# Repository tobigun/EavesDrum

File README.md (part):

<p align="center">
  No matter if you are E(a)ve or Ste(a)ve - drumming for e(a)veryone
</p>

<p align="center">

</p>

<!-- vscode-markdown-toc -->
- [Welcome to EavesDrum!](#welcome-to-eavesdrum)
  - [Downloads](#downloads)
  - [EavesDrum Trigger Module](#eavesdrum-trigger-module)
- [Features](#features)
- [Before You Start: Is EavesDrum What You Need?](#before-you-start-is-eavesdrum-what-you-need)
- [Getting Started](#getting-started)
- [Build Your Own EavesDrum Trigger Module](#build-your-own-eavesdrum-trigger-module)
  - [Use the Reference Design](#use-the-reference-design)
    - [PCB Ordering and Assembly](#pcb-ordering-and-assembly)
    - [Connector Harness](#connector-harness)
      - [Connector Module](#connector-module)
      - [Build your own adapter](#build-your-own-adapter)
      - [Wiring the Single Pad Connectors](#wiring-the-single-pad-connectors)
  - [Make Your Own Design](#make-your-own-design)
    - [How the Circuit Works](#how-the-circuit-works)
      - [Over-Voltage Protection](#over-voltage-protection)
      - [Voltage Divider / DC Voltage Offset Generator](#voltage-divider--dc-voltage-offset-generator)
      - [Example](#example)
- [Configuration](#configuration)
  - [Calibration](#calibration)
  - [Settings](#settings)
    - [Generic Settings](#generic-settings)
    - [Pedal Settings](#pedal-settings)
    - [Apply Presets](#apply-presets)
  - [Mappings](#mappings)
  - [Apply a Whole Configuration](#apply-a-whole-configuration)
- [Understand and Reduce Latency](#understand-and-reduce-latency)
  - [Reduce Hit Detection Latency](#reduce-hit-detection-latency)
  - [Reduce Audio Interface Latency](#reduce-audio-interface-latency)
  - [TL;DR](#tldr)
- [Firmware Development](#firmware-development)
  - [How to Build the UI](#how-to-build-the-ui)
  - [How to Build the Backend and Firmware](#how-to-build-the-backend-and-firmware)
  - [How to Simulate a Drum-Kit on a PC](#how-to-simulate-a-drum-kit-on-a-pc)
- [FAQ](#faq)
    - [Windows 10 NCM device driver](#windows-10-ncm-device-driver)
- [About This Project](#about-this-project)
- [Other Related Projects](#other-related-projects)
- [Libraries](#libraries)
- [Author](#author)
- [License](#license)

<!-- vscode-markdown-toc-config
	numbering=false
	autoSave=true
	/vscode-markdown-toc-config -->
<!-- /vscode-markdown-toc -->

## Welcome to EavesDrum!

EavesDrum is an open-source e-drum trigger module project designed for drummers and makers.

It allows you to connect a multitude of drum pads or piezo triggers and convert their signals into MIDI events.

The configuration of the module is simple and user-friendly, thanks to a built-in WebUI. You can adjust sensitivity, threshold, and other parameters directly from your browser—no need for complicated software or direct hardware programming.

The trigger module acts as a USB MIDI device - simply connect it to your notebook and use drum software of your choice (EZdrummer, Addictive Drums, SSD5, ...) to convert your notebook into a complete drum module.

### Downloads
- Trigger Module:
  - [PCB files](https://github.com/tobigun/EavesDrum/releases/tag/PCB-module-v1.1.1)
  - [Firmware](https://github.com/tobigun/EavesDrum/releases/latest)
- [DIY Optical Hi-Hat Sensor](doc/hihat.md)

### EavesDrum Trigger Module

DIY ultra-low-volume metal mesh cymbal setup:

Conventional rubber cymbal setup:

Low-volume cymbal setup:

System overview:

## Features

- **Drum Trigger Inputs:**
  - With the EavesDrum PCB, you can connect your drum pads or piezo sensors to 32 analog inputs.
  - Each input can be mapped individually, for example to 16 TRS (3-pin Tip-Ring-Sleeve) connectors or 32 TS (2-pin Tip-Sleeve) connectors.
  - The [default configuration](#connector-harness) uses the following drum setup:
    - Snare (1x TRS for head/rim + 1x TS for side-rim)
    - 5x Toms (each with 1 TRS for head/rim)
    - Kick drum (1x TS)
    - Ride (1x TRS for bow/edge + 1x TS for cup)
    - 4x Cymbals (each with 1x TRS for bow/edge + 1x TS for cup)
    - Hi-Hat (1x TRS for bow/edge + 1x TS for cup)
    - Hi-Hat Pedal resistive or optical (connected to a dedicated connector with 3.3V or 5V supply voltage)
- **Compatibility:**
  -  EavesDrum is compatible with a wide range of [Roland (only non-USB), Yamaha, ATV and EFNOTE pads](#pad-connectors).
  -  The following pads were tested:
     - ATV XD-P10M/P13M 2-zone Drums
     - ATV aD-C14/C16/C18 3-zone Cymbals
     - EFNOTE EFD-S12P 3-zone Snare (head, rim, side-rim)
     - Roland PDX-8 2-zone Drum
     - Roland KD-10 Kick Pad
     - Zeitgeist ZG ECP 13" 3-zone Cymbal
     - Zeitgeist ZG CAD Cymbals (although the edge triggers unreliably due to the switch design)
     - Zeitgeist ZG ZKD7 Kick Pad
     - Drum-tec Hi-Hat controller (resistive)
     - DIY optical sensor (TCRT5000 based)
       - See sections below for schematics and Gerber files.
     - DIY drums and cymbals
       - See sections below for schematics and Gerber files.
- **MIDI Output:**
  - USB Device (Default)
    - Connect EavesDrum to a PC and use a Drum Software like EZdrummer or Superior Drummer to convert the trigger signals to high quality drum sounds. 
  - USB Host
    - Connect a USB device to EavesDrum, e.g. a Drum Module and trigger sounds on that device
      - Tested with a Yamaha EAD-10
      - Device must be compatible with USB Full-Speed device. This does not apply to EFNOTE's 3/5/7 devices as they require a USB High-Speed device.
  - DIN 5-Pin
    - Connect legacy drum modules or devices that still have a DIN 5-pin connector and trigger sounds on them.
  - Bluetooth LE Client (Pico2W only)
    - This can be used to connect to a device that can act as a Bluetooth LE MIDI Server, e.g. EFNOTE's 3/5/7 drum modules.
  - Bluetooth LE Server (Pico2W only)
    - Activate the BLE Server mode and connect a smartphone or tablet to EavesDrum and trigger sounds in an app. This can also be used to connect a computer wireless.
      - Android (smartphone): works, but most MIDI apps will require the "MIDI+BTLE" app to use BLE as they do not support it directly.
      - Windows (PC): does not support BLE MIDI out-of-the-box. You will need a BLE connector app like [BLE-MIDI Bridge](https://github.com/Maxime-J/BLE-MIDI-Bridge) or [MIDIberry](https://apps.microsoft.com/detail/9n39720h2m05) together with a virtual loopback MIDI cable software like [loopMIDI](https://www.tobias-erichsen.de/software/loopmidi.html).
      - iOS (iPad): works with Garage Band out of the box
  - Guitar Hero Drum-Kit (SPI)
    - If you have an old Guitar Hero Drum-Kit (e.g. for the Wii), attach EavesDrum to the controllers internal SPI connector and play Guitar Hero on your retro console with your modern drum kit.
- **MIDI Mappings:** 
  - Mappings are freely customizable via the UI.
  - It already contains Midi-Mappings for:
    - Addictive Drums 2
    - BFD Player 1.2
    - EZdrummer 3 (which can probably also be used as a base for your own Superior Drummer 3 mapping)
    - Superior Drummer 3
    - MT Power 2
    - Steven Slate Drums 5 (SSD5)
- **Low Latency:**
  - Latency is mainly determined by your audio interface and the selected scan time. With a decent audio interface, you can [reach a total latency of about 8ms](#latency).
  - You can measure the latency of your setup with the latency measurement feature built into the UI.
- **Affordable:** you might be able to make an assembled trigger module for approx. 20€.
  - See the section [Build your own EavesDrum trigger module](#use-the-reference-design).
- **Supported Microcontrollers:**
  - Raspberry Pi Pico2
  - Raspberry Pi Pico2W (comes with a WIFI and Bluetooth module)
    - Required for MIDI over Bluetooth LE.
    - Also provides a WIFI Access Point to reach the EavesDrum WebUI wirelessly. 

- **Open Source:** Source code and PCB Gerber files are available for customization and extension.
- **WebUI Configuration:** Browser-based interface for setting up and tweaking trigger parameters such as sensitivity, threshold, retrigger prevention, and more. No app required as the UI runs directly on the trigger module.
  - Monitor the signal of your drum pads in real time so that you can see the effect of your settings.

  - Provides extensive settings options within a (hopefully) user-friendly layout.

  - Mappings can be adjusted individually or for the whole kit.

## Before You Start: Is EavesDrum What You Need?
**EavesDrum is for you if you:**
  - need more / additional trigger inputs to those that standard drum kits support.
  - want to mix drums from different vendors as most drum kits only work well with their own pads.
  - want to start drumming and do not want to pay a fortune for a drum kit.
  - want to diagnose or improve the trigger behavior of your drum pad.
  - have fun making stuff and just want to build your own drum kit or implement your own drum module features.

**EavesDrum might not be for you if you:**
  - want to use the module for live performances as it does not give any guarantee error-free operation at all times or conditions.
  - want a drum module that works standalone without a Notebook.
  - want a drum module that works out-of-the-box, as you will have to tweak the settings according to your pads via the UI.
  - need cross-talk cancelation, positional sensing or decay curves, as these features are not implemented (yet).

> [!IMPORTANT]
> **Disclaimer:** Although EavesDrum has been tested with various drum pads and setups, it remains a DIY hardware project and may behave differently depending on your specific configuration. Connecting this module to your equipment is done at your own risk. I cannot be held liable for any damage, malfunction, or injury resulting from its use. Please ensure compatibility and take appropriate precautions before integrating it into your setup.

## Getting Started

0. **Prerequisites:**
All you need is:
    - A computer with a drum software (see [MIDI Mappings](#midi-mappings) to give you a short overview).
      - A PC or Mac is recommended.
        - Although there is no minimum requirement, a slow CPU might increase the [Latency](#latency).
        - USB and Bluetooth LE is supported
      - An Apple iPad with Garage Band also works - either with USB-C (or an Apple Camera Connection Kit for Lightning connectors) or with Bluetooth LE.
      -  Android smartphones / tablets also work (via USB or Bluetooth LE) but lack good drumming apps.
    - A decent audio interface with low latency, preferably one with dedicated ASIO drivers. See [the section about latency](#latency) for more information.
    - Something to drum on, i.e. drum pads, cymbals and a Hi-Hat pedal. Or just a cheap piezo if you want to DIY your own drum.

1. **Build the EavesDrum trigger module:**<br/>
   - Either built it yourself or order it via a PCB manufacturer of your choice.
   - See section [Build your own EavesDrum trigger module](#use-the-reference-design) for schematics and Gerber files.

2. **Download & Flash the firmware:**<br/>
   - [Download the firmware for your Pico board from the Release download section](https://github.com/tobigun/EavesDrum/releases/latest).
   - Press the BOOTSEL while connecting your Pico Board via USB to enter the bootloader mode.
   - The board will now be detected as an USB flash drive.
   - Drag & Drop the firmware .uf2 file onto the drive.
3. **Start the WebUI:**<br/>
   - Connect EavesDrum to a computer, tablet or smartphone
     - via USB: EavesDrum will be detected as a network device
     - via WIFI AccessPoint (only with Pico2W)
       - The AccessPoint (AP) can be activated by pressing and holding the WIFI button at power-up until the network LED lights up. For security and performance reasons, the AP is only active for one session until the module is powered down.
       - Connect to the AP named "EavesDrum". No credentials are required.
   - Open your browser and navigate to the WebUI by entering either
     - the static IP: http://192.168.7.1 (USB) or http://192.168.4.1 (WIFI AP)
     - the DNS name http://eaves.drum</a>.
     - **IMPORTANT**: if you are using Windows 10 you have to install the USB network drivers manually to reach the WebUI. See the [FAQ](#faq) section below for more info. 
4. **Calibrate:**<br/>
   - [Calibrate the voltage offset with the UI Wizard](#calibration)
5. **Connect Drums:**<br/>
   - Connect your drum pads or triggers to the EavesDrum hardware.
6. **Configuration:**<br/>
   - Adjust [settings](#settings) and [MIDI mappings](#mappings).
7. **Play:**<br/>
   - Once configured, start playing and enjoy!

## Build Your Own EavesDrum Trigger Module
### Use the Reference Design
**Schematics of the trigger module with 32 inputs:**

You can find the schematics and pcb files in the `schematics/module` directory. They can be viewed and edited with [KiCad](https://www.kicad.org/).

**Bill of material (BOM):**

| Component | Designator | Quantity | Price / Unit | Price Total | Comment |
| --------- | ---------- | -------- | ------------ | ----------- | ------- | 
| Raspberry Pi Pico 2(W)(H) | A1 | 1 | 5€ / W: 7.50€ | 5€ / W: 7.50€ | Use a Pico2W if you want WiFi and Bluetooth LE, otherwise a Pico2 is enough.<br>- There is also a "H" variant for ~1€ more with an already soldered header<br>- Pico1 is not recommended due its outdated performance. |
| 20-pin Header (male)<br>20-pin Header (female) | J4, J5 | 2 | 0.20€<br>0.30€ | 1.00€ | Optional but recommended. <br>- Socket your Pico so that it can be replaced if it is damaged or if you want to exchange it by another variant.<br>- The male header is not needed if one of the Pico "H" variants is used. |
| HC4067 | U1, U2 | 2 | 1.00€ | 2.00€ | Multiplexer. Each provides 16 inputs.<br>Available from many vendors with HC4067 in the name (e.g. CD74HC4067M). Make sure it is the SO-24 package. |
| BAT54S | D1.0 - D1.15<br>D2.0 - D2.15 | 32 | 0.05€ | 1.60€ |Prefer the ones with a forward voltage (VF) of 800mV@100mA over those with 1V@100mA but probably any vendor and type will work.|
| LED (red) | D3 | 1 | 0.08€ | 0.08€ | Use any color of your choice. THT or SMD 0805 / 0603 packages are supported. |
| LED (white/blue) | D4 | 1 | 0.10€ | 0.10€ | Use any color of your choice. THT or SMD 0805 / 0603 packages are supported. |
| LED (yellow) | D5 | 1 | 0.10€ | 0.10€ | Use any color of your choice. THT or SMD 0805 / 0603 packages are supported. |
| Push Switch | SW1, SW2, SW3 | 3 | 0.15€ | 0.45€ |6x6mm. Only the `RESET` button is used at the moment. |
| Potentiometer 5k | R3, R6 | 2 | 0.35€ | 0.70€ | Supports Piher PT10 (10mm) / PT6 (6mm) or Bourns TC33 (SMD) |
| Potentiometer 100k | R11 | 1 | 0.35€ | 0.35€ | Supports **only** Piher PT6 (6mm) or Bourns TC33 (SMD) |
| Resistor 10 Ohms | R17 | 1 | 0.03€ | 0.03€ | SMD 0805 package, 125mW, 1%.<br>For MIDI 5-pin DIN connector |
| Resistor 33 Ohms | R18 | 1 | 0.03€ | 0.03€ | SMD 0805 package, 125mW, 1%.<br>For MIDI 5-pin DIN connector |
| Resistor 330 Ohms | R5, R8, R13 | 3 | 0.03€ | 0.09€ | SMD 0805 package, 125mW, 1% |
| Resistor 1 kOhms | R1.0 - R1.15<br>R2.0 - R2.15 | 32 | 0.015€ | 0.48€ | SMD 0805 package, 125mW, 1% |
| Resistor 2.7 kOhms | R4 | 1 | 0.03€ | 0.03€ | SMD 0805 package, 125mW, 1% |
| Resistor 4.7 kOhms | R9, R14 | 2 | 0.03€ | 0.06€ | SMD 0805 package, 125mW, 1%.<br>Use different values to adjust brightness of LEDs D3 (R9) and D5 (R14) to your liking. |
| Resistor 10 kOhms | R10 | 1 | 0.03€ | 0.03€ | SMD 0805 package, 125mW, 1%<br>Use different value to adjust brightness of LED D4 to your liking. |
| Resistor 15 kOhms | R15, R16 | 1 | 0.03€ | 0.06€ | SMD 0805 package, 125mW, 1%.<br>For USB-Host connector |
| Capacitor 10 µF | C1, C2 | 2 | 0.04€ | 0.08€ | SMD 0805 package, >=25V, X5R (or X7R)
| D-Sub HD 44-pin Connector, right-angled, female | J0 | 1 | 2.50€ | 2.50€ | Alternatively, you can use any connector of your choice via the 2x25 pin IDC header (J2). |
| USB-A socket, right-angled | J1 | 1 | 0.15€ | 0.15€ | Socket for USB-Host. |
| Header 2x25 pins (male) | J2 | 1 | 0.33€ | 0.33€ | Expansion port (Optional).
| 3-Pin Header (female) | J3 | 1 | 0.15€ | 0.15€ | UART serial debug output.
| DIN 5-pin female 180° | J7 | 1 | 0.85€ | 0.85€ | Connector for MIDI Serial DIN Output. |
| PCB | - | 1 | ~5€ (Germany) | ~5€ | See the section [PCB Ordering and Assembly](#pcb-ordering-and-assembly) for more info|
| **Total** |||| ~22€ || 

If you are located in Germany, check prices at Reichelt (that's where the prices from above are from), Pollin, Conrad. Globally Mouser and Farnell might be your friend.

#### PCB Ordering and Assembly
All you need to order your Trigger Module PCB for assembly are the following files:
- GERBER File
- BOM File (Bill of Material)
- CPL File (Component Placement List)

These files are available on the [PCB Module 1.2 Release Page](https://github.com/tobigun/EavesDrum/releases/tag/PCB-module-v1.2).

**To order the PCB:**
- Open the website of a PCB manufacturer.
  - The most famous ones are probably JLCPCB and PCBWay from China.
  - There is also Aisler (Germany), EuroCircuits (Europe) and probably more if you want to produce your PCB in Europe instead of China.
  - Choose whatever suits you best.
- Upload the GERBER zip-file. The site should show you a preview of the PCB now.
- You can leave the default settings.
  - (Recommended) Change `Surface Finish` from `HASL (with lead)` to `LeadFree HASL` to protect our environment from toxic lead
- For delivery "EuroPacket" or "Global (Standard) Direct" might be your choice.
  - Both variants will ship your PCBs together with other PCBs in a big package to an importer in your home country (or a neighbored country). The package will then be split into smaller packages and sent to you. This is cheaper and will probably also save you the hassle of customs as this will be done by the importer.
  - The shipment time is a bit longer than with other more expensive delivery options. But with all options the parcel will probably spent several days in the customs office, so time savings is not that much noticable.

*Examples:*
- JLCPCB: 4€ - Coupons + Shipping/Taxes
  - Shipping to Germany: Global Standard Direct: 1.50€ / EuroPacket: 5.50€ + Tax: ~1€
- PCBWay: 5€ - Coupons + Shipping/Taxes
  - Shipping to Germany: ~5€ with Global Direct + Tax: ?

Due to the varying discount by coupons, prices of JLCPCB and PCBWay my vary. So check both.

**Assembly**
It is possible to assemble the PCB on your own by hand-soldering without special equipment. The only tricky part is the HC4067 SMD packages and the SMD resistors and capacitors. While the latter is quite easy, the HC4067 requires some experience.

You can also let JLCPCB or PCBWay assemble the PCB as you already order the PCB there.

*Example:*
- JLCPCB: 5 assembled PCBs including parts cost about 106€ (excl. shipping/tax), so approx. 21€ per PCB.
  - Note that the minimum amount of assembled PCBs per order is 2

If you want an assembled board it is best to organize a collective purchase order to split the cost. I created a [forum discussion where you can organize an order](https://github.com/tobigun/EavesDrum/discussions/1).

**To order an assembled PCB:**
- Perform the same steps as for the normal PCB but select "PCB Assembly".
- If you use JLCPCB in the next step you are asked for the BOM and CPL files that you have to upload.
- Some parts might currently not be available. There is most likely an identical component / chip from a different vendor that you can select in this case.
- In the next step check the component placements and submit your order.
- After a review an engineer might contact you if there are questions about the design (that was the case in my order).

> [!NOTE]
> Also take a look at the [DIY Optical Hi-Hat Sensor PCB](doc/hihat.md). You might want to get both PCBs with one order.

#### Connector Harness

In addition to the trigger module you will have to build an adapter to connect the drum pads.

##### Connector Module

The easiest way to achieve this is to build the connector module:

You can find more information about the connector and the files to order the (assembled) PCB on the  
[connector release page](https://github.com/tobigun/EavesDrum/releases/tag/PCB-connector-v1.0).

##### Build your own adapter

But you can also build your own adapter. Here is the pin out of the D-Sub HD 44 pin connector:

The pin names consist of the multiplexer input IDs (in1_x: input x of Multiplexer MP1, in2_x: input x of Multiplexer MP2).

You can either solder jacks directly to a D-Sub connector or you can build an adapter to one of the cable harnesses that come with drum modules.

This is the default configuration for the outputs:

| Jack | Pins | Assignment |
|-----------|------|------------|
|1| in1_0, in1_1, in1_2 | Snare (Main, Rim, Side-Rim) |
|2| in1_3, in1_4 | Tom 1 (Main, Rim) |
|3| in1_5, in1_6 | Tom 2 (Main, Rim) |
|4| in1_7, in1_8 | Tom 3 (Main, Rim) |
|5| in1_9 | Kick Drum |
|6| in1_10, in1_11, in1_12 | Ride (Bow, Edge, Cup) |
|7| in1_13, in1_14, in1_15 | Cymbal 1 (Bow, Edge, Cup) |
|8| in2_0, in2_1, in2_2 | Cymbal 2 (Bow, Edge, Cup) |
|9| in2_3, in2_4, in2_5 | Cymbal 3 (Bow, Edge, Cup) |
|10| in2_6, in2_7, in2_8 | Hi-Hat (Bow, Edge, Cup) |
|11| in2_9, in2_10 | Tom 4 (Main, Rim) |
|12| in2_11, in2_12 | Tom 5 (Main, Rim) |
|13| in2_13, in2_14, in2_15 | Cymbal 4 (Bow, Edge, Cup) |
|Pedal| adc2, +3.3V/5V (optical only) | Hi-Hat Pedal (resistive or optical)<br>- For resistive controllers: adjust the `ADC2 DC offset` potentiometer to the (+) direction (~4kOhm)<br>- For optical (TCRT5000) controllers: adjust the `ADC2 DC offset` potentiometer to the middle (~69kOhm)<br>This will adjust the sensitivity of the ADC2 channel. You can fine-tune this setting in the UI later. |

> [!INFO]
> The layout for the older D-Sub 37 pin connector of board revisions v1.1.x can be found [here](https://github.com/tobigun/EavesDrum/tree/PCB-module-v1.1.1#connector-harness)

##### Wiring the Single Pad Connectors

The wiring of **Snares and Toms** is straightforward in most cases
- Almost all companies use the Roland style 2-Piezo 1xTRS layout
- Yamaha uses switches for Edge and Side Rim
- EFNote adds a dedicated Side-Rim zone with another Piezo

<table>
<thead>
  <tr>
    <th>Tom/Snare</th>
    <th>Main/Head (Piezo)</th>
    <th>Edge</th>
    <th>Side-Rim</th>
    <th>EavesDrum Setting</th>
  </tr>
</thead>
<tbody>
  <tr><td>Generic 1-Zone</td><td>Tip</td><td>-</td><td>-</td><td>Drum / 1-Zone / Piezo</td></tr>
  <tr><td>Roland 2-Zone</td><td>Tip</td><td>Ring</td><td>- (Cross-Stick sound is generated by module)</td><td>Drum / 2-Zones / 2 Piezos</td></tr>
  <tr><td>Yamaha 3-Zone</td><td>Tip</td><td colspan='2'>Ring (Switches for zones are multiplexed by a 10k resistor)</td><td>Drum / 3-Zones / Piezo + 2 Switches (1x TRS)</td></tr>
  <tr><td>EFNOTE 3-Zone</td><td>Tip (Main Jack)</td><td>Ring (Main Jack)</td><td>Tip (Side-Rim Jack)</td><td>Drum / 3-Zones / 3 Piezos</td></tr>
</tbody>
</table>

**Cymbals** (with 3-Zones) follow two main connection styles:
- Roland style with 2x TRS Jacks (labeled "Bow/Edge" and "Bow/Bell")
- Yamaha style with 1x TRS Jack. Bell and Cup switch connected to the "Ring" pin (multiplexed by a 10k resistor)

If you have only a one or two zone cymbal the pin layout is the same for both vendors.

<table>
<thead>
  <tr>
    <th>Cymbal</th>
    <th>Bow (Piezo)</th>
    <th>Edge Switch</th>
    <th>Bell/Cup Switch</th>
    <th>EavesDrum Setting</th>
  </tr>
</thead>
<tbody>
  <tr><td>Generic 1-Zone</td><td>Tip</td><td>-</td><td>-</td><td>Cymbal / 1-Zone / Piezo / No Choke</td></tr>
  <tr><td>Generic 2-Zone</td><td>Tip</td><td>Ring</td><td>-</td><td>Cymbal / 2-Zones / Piezo + Switch / Choke: Edge</td></tr>
  <tr><td>Roland 3-Zone</td><td>Tip (Jack "Bow/Edge")</td><td>Ring (Jack "Bow/Edge")</td><td>Ring (Jack "Bow/Bell")</td><td>Cymbal / 3-Zones / Piezo + 2 Switches (<b>2x</b> TRS) / Choke: Edge</td></tr>
  <tr><td>Yamaha 3-Zone</td><td>Tip</td><td colspan='2'>Ring (multiplexed by a 10k resistor)</td><td>Cymbal / 3-Zones / Piezo + 2 Switches (<b>1x</b> TRS) / Choke: Edge</td></tr>
</tbody>
</table>

See also:
- [Cymbal wiring diagram at edrums.github.io](https://edrums.github.io/en/diy/cymbal_switch/) for the wiring difference between Roland and Yamaha cymbals.
- [Yamaha compatibility matrix](https://de.yamaha.com/de/download/files/2094396/) for an overview of the Tom and Cymbal models

### Make Your Own Design

In case you do not want to use the reference design or you just need a few inputs, you can also design your own trigger module and just use the firmware.
The base circuit for each input consists of the following parts:

Please note that "~2,7k" for R1 in the schematics means that the variable resistor should be adjusted to this value. The nominal value of the resistor should be about 5k to have some range for the adjustment.

You might also be able to build this on a breadboard for first experimentation.

#### How the Circuit Works
Skip this section if you are not interested in the electronic background of the circuit.

##### Over-Voltage Protection
- Two clamping diodes restrict the signal to the range between 0V - 3.3V
  - Protects the ADC input pins of the microcontroller
  - Prevents cross-talk between inputs if a Multiplexer (e.g. 74HC4067) is used
- Note that Schottky diodes with a low forward voltage have to be used here
  - They react faster than a conventional (Silicon P-N-junction) diode to over voltage spikes
  - The BAT85, BAS85 (SMD variant of the BAT85) and BAT54S (two diodes in one SMD package) diodes work fine

##### Voltage Divider / DC Voltage Offset Generator
- The resistors R1 and R2 form a voltage divider that halfs the operation voltage (Vcc=3.3V) to generate a ~1.65V DC offset voltage
  - This is necessary to sample the full signal with its positive and negative half-wave
  - Note that R1 is a variable resistor (potentiometer) as the circuit is usually not that perfect that R1=R2 gives you half the operation voltage as it should in theory
- Together with R3, R1 and R2 scale the voltage of the piezo to the range of 0V - 3.3V that can be sampled by the ADC
  - This is necessary as the voltages of a piezo can be rather high.
  - If you want to play with the values there is an [LTSpice simulation here](doc/simulation/drum-trigger.asc) but keep in mind that the piezo model does not act like a real one.
- Simpler approaches without an offset voltage are also possible, e.g. by just clamping the signal with a zener diode to just keep the positive half-wave of the signal
    - Although this works, you will have to pay attention to the polarity of the piezos
    - If the piezo starts with a negative half-wave, you will miss it and thus will add latency of approx. 1ms
    - This is even worse, if you use two piezos for head and rim, as the wrong zone might be triggered if the first half-wave of one piezo is missing but missing for the other.

##### Example
Here is a simple example with a high intensity hit on a snare drum: The left shows the input signal that is offset by 1.65V and it fits nicely into the 0V - 3.3V range. On the right you see the display in the UI. All the details of the signal are maintained. Note that the firmware maps the negative part of the signal to the positive y-axis so that the thresholds can be edited more easily.

## Configuration

### Calibration
Before you can start you have to first adjust the DC voltage offset so that the signal level is at 0% when no pad is hit. But no panic - the process is easy and only has to be done once.

For this open the WebUI, open the settings page (should be open by default) and click on `Calibrate` in the `Monitor` panel and follow the instructions.

At the beginning the signal graph will probably look like this, with a signal level above 0% (here 10%):

Now turn the potentiometer labeled `ADC0 DC offset` (R3) with a screwdriver. Only if turned in the correct direction, the signal level will decrease, otherwise it will increase. So turn the potentiometer until the signal level reaches 0%. If you turned too much, the signal level will increase again - in this case turn in the opposite direction.

The signal graph should now look like this - with a signal level of 0%:

Now the calibration is completed.

> [!NOTE]
> Do not worry if the signal is not totally clean and has a bit of a ripple in the 1% or 2% range. This can be compensated with the thresholds later.
> If you do not reach the 0% level at all, your trigger module might be faulty.

### Settings

To optimize the trigger behavior for your pad, go to the settings page and open the panel of the pad you want to adjust.

First assure that the Drum type (here: Drum / 3-Zones / 3 Piezos) is correct. If you are not sure, check [the section about the different pad connectors](#pad-connectors) to see what the type should be.

Mark the pad as monitored (the record button on the right top of the pad's panel). This way you can see the signal graph (left) and hit graph (right) in the `Monitor` panel whenever you hit the monitored pad. Right next to the hit graph is the hit history which shows you the last hits. You can also click on one of the last hits to see the graphs again.

If you click on `Show All Pads` on the top, you can see hits on every pad, no matter if it is monitored or not.

#### Generic Settings

- **Main/Head/Rim/Edge/Cup/... Range**: trigger range for each zone
  - The **min. value of the range** specifies the sensitivity.
    - You should set it as low as possible without having the pad trigger when you do not hit it.
  - The **max. value of the range** specifies the signal level that marks 100%.
    - Set it in a way that you can reach a signal level of 100% when you hit the pad the hardest way you would in your playing style.
    - If you set the max. too low, the detected signal level will be 100% even if you did not hit the pad with the highest intensity.
  - If you enable monitoring for the pad it should be easy to find the correct values.
  - For cymbals with switches for edge and cup you will only have a **minimum threshold** for each switch instead of a range.
    - This determines at which level the switch is considered to be closed or opened.

- **Scan Time**: Determines the time to search for a peak (Scan phase).
- **Mask Time**: Blocks hit detection for the given time (Mask phase).
  - Can be used to reduce false retriggers.
  - The Mask phase starts after the Scan phase.
  - The Mask is applied to all zones of the pad.
- **Decay Time**: Blocks hits with a hit velocity below the given decay curve (Decay phase).
  - In contrast to the Mask phase that blocks all hits, this only blocks hits selectively.
  - It can be used to define a longer decay phase where reverberations of the last hit can be blocked but new hits are still possible if they are strong enough.
  - The Decay phase starts after the Mask phase.
  - The Decay curve is applied to all zones of the pad.
- **Decay Curve**: The curve that defines how the detection threshold decreases during the decay phase.
  - **Linear**: The further the decay phase progresses, the lower the required hit strength becomes for a hit to be detected. 
    - The phase begins with a detection threshold equal to the highest signal value detected during the scan phase (the peak).
    - It ends with a detection threshold equal to the minimum detection threshold.
    - Throughout the decay phase, the threshold is linearly reduced from the peak value down to the minimum threshold.
- **Curve Type**: Lets you change the trigger behavior for low or high intensity hits, i.e. you can shift the sensitivity more to the lower or higher intensities.
- **Head/Rim Bias**: Sets whether to prefer head or rim sound when the signals of both to not indicate a clear winner.
  - This is useful to assure that rimshots trigger the rim sound.
  - Move the bias more to the rim (i.e. to the right), the rim zone will more likely be triggered if both zones were hit at once.
  - Only available for drums (i.e. snares and toms) with at least two zones.

> [!IMPORTANT]
> When you change settings they will be applied immediately but they will be reset to the old values when EavesDrum reboots or loses power. To keep the settings you have to save them with the "Save" Button (SD-Card icon) in the top Icon Bar.

#### Pedal Settings
The settings for the Hi-Hat pedal are different from the settings of the pads.

- **Pedal Range**: determines the offset and threshold for the lowest and highest signal level
  - Do not touch the Hi-Hat pedal for the open position.
  - Adjust the **min value** of the `Pedal Range` so that the corresponding marker in the monitor's signal graph is slightly above the current pedal signal and the Pedal value in the hit graph is at 0%.
  - Next, close the Hi-Hat pedal.
  - Now adjust the **max value** of the `Pedal Range` so that the corresponding marker in the monitor's signal graph is slightly below the current signal and the hit graph shows 100%.
  - When you move the pedal now, you should get the full range between 0% and 100% in the hit graph, and it should stay at 0% when open and at 100% when closed.
- **Move Detection Tolerance** this determines how much the pedal has to be moved to change its value. A smaller tolerance gives you a higher resolution but is more prone to noise in the signal.
  - Press the Hi-Hat pedal to a position between open and closed. Try to keep this position - the value in the hit graph should not change. If it does, you might decrease the tolerance until the hit graph value is stable.
- **Pedal State Thresholds** and **Chick Detect Timeout**:
  - When the pedal travels from the `Almost Closed` position to the `Closed Position` a "Chick" sound detection takes place.
  - The faster the pedal moves from `Almost Closed` to `Closed` the higher the intensity of the "Chick" sound will be.
  - If the time between both states is higher than **Chick Detect Timeout**, then no sound will be played.
  - If you do not want a "Chick" sound, you can disable it on the Mappings Page by setting the sound for the "Chick" to `None`.

To see the effect of the settings, monitor the pedal with the record button:

#### Apply Presets
In the folder `config/presets` you can find some presets for some pads. You can apply them by dragging them from Windows Explorer to the settings panel of a pad.

### Mappings

With the Mappings page you can change the MIDI mappings of each pad.

Select the MIDI note of the zone to the desired value. You can trigger the note via the UI by pressing the "Play" button to preview the sound.

> [!IMPORTANT]
> When you change mappings they will be applied immediately but they will be reset to the old values when EavesDrum reboots or loses power. To keep the settings you have to save them with the "Save" Button (SD-Card icon) in the top Icon Bar.

**Apply Drum-Kit Mappings**
You can change the mappings of all pads in the drum-kit at ones if you drag & drop a mapping file (see folder `/config/mappings`) to top border (aka the Icon Bar) of the UI. This way you can switch between the mappings of the drum softwares easily.

Alternatively you can also click on the "Apply Config File" button in the top Icon Bar to open the same file drop area that appears if you drag & drop a file.

If you drag & drop the mappings file onto a pad instead of the top bar, only this pad's mappings will be changed:

**Roles**
Note that the mappings are assigned to a `role` (e.g. Snare, Tom1, ...) and not to a pad directly. As the drum kits differ in number and type of pads it would be rather difficult to have generic mapping files if there is no common denominator for every drum. This is what the role is for: it specifies the role of the drum in the drum kit, so that you have the correct mappings assigned to the drum when you switch from one mapping file to another.

### Apply a Whole Configuration
If you want to have more control over a configuration you can download the active configuration with the "Download" icon in the top Icon Bar. Then do you modifications on the downloaded YAML file and upload it again by either clicking on the "Apply Config File" button in the Icon Bar or by Drag & Drop of the config to the Icon Bar.

This way you can Backup & Restore your config whenever you do a firmware update.

## Understand and Reduce Latency
At a speed of sound of about 343 m/s, the sound travels 34 cm in 1 ms, so a little less then the length of a drum stick. It seems that everything up to [5 ms is not noticeable and most drummers still have no problem with 10 ms](https://forums.steinberg.net/t/ab-welcher-latenz-bemerkt-ihr-eine-verzogerung-und-ab-wann-stort-die-euch/105517/45). So you want the latency to be as low as possible or at least below 10 ms.

If you look at the signal path there a quite some components involved from the hit to the drum until you hear the sound from the speaker. This is round trip time (RTT) of your system which defines the latency of your signal.

1. The **hit detection** by the trigger module will take a fixed time - the scan time that you selected in the pad's settings and that is by default 3 ms.
1. The time it takes the trigger module to **generate and transfer a MIDI message to the computer via USB** is negligible as it is only a small fraction of a ms.
2. Although the **sound processing** might also take some time I did not notice a vast differences between the drum softwares.
3. The audio latency from your drum software to the **audio interface** is the biggest contributor to latency.

### Reduce Hit Detection Latency
The time the trigger module waits for a peak to detect a hit can be configured for each pad. The default of 3 ms was chosen so that it works with most drum pads.

If you take a look at the screenshot of the Monitor below you might notice that the piezo signal for some pads reaches its peaks only after 1, 2 or even 3 ms. 

So if you set the scan time too low, you might get wrong results. Decrease the scan time in small amounts and check if the hit strength are still detected correctly.

### Reduce Audio Interface Latency
The Audio Interface latency depends on the **number of buffers** the software, drivers and audio interface uses and the **buffer size**.
  - Dedicated audio interfaces for musicians are optimized for low latency and offer better (ASIO) drivers.
  - The bigger the buffer the less error-prone is the playback, even if the CPU is currently doing some other stuff. But every buffer and every byte in the buffer will increase the latency.

The best way to reduce latency is to **reduce the buffer sizes**. The goal is a **latency of 5-6 ms** for this part of the signal chain.
  - On **Windows** this is **only possible** without crackling and dropouts **with ASIO drivers**. So make sure your audio device has dedicated ASIO drivers.
  - Do not waste your time with **WASAPI** or **DirectSound** drivers. WASAPI (Low-Latency) resulted in 69ms, WASAPI (Exclusive Mode) in 34.9ms. DirectSound was even worse. Same device with ASIO was about 6ms.
  - You can try **[ASIO4All](https://asio4all.org/)** if you want to start with an existing interface that does not come with ASIO drivers - but keep your expectations low. With the Realtek soundcard built into one of my notebooks I could not get the latency below 35 ms with ASIO4All which is unusable.

**Select ASIO as the output type** in your drum software and start with the lowest audio buffer size.
  - Trigger the pads really quick and try every pads if you hear some crackling or dropouts on any of them.
  - Also check if the audio quality is still ok or if it sounds muffled, ...
  - If you notice audio problems (**crackling, muffling, popping, dropouts**)
    - Make sure that no other CPU-intensive software is currently in use.
    - Also make sure that your CPU is suited for the task (i.e. you CPU load is not too high)
    - Although my old Intel Core i7-7500U (2.7 GHz) Ultrabook CPU from 2016 works fine as drum computer most of the time, it seems to stutter sometimes if I select the lowest buffer size. Something I have not noticed with my newer Intel Core i7-1260P (2.1 GHz, 12 Cores) from 2022.
    - If you have a modern i7 (and probably i5) CPU you should be fine. Same with an Apple M1 CPU.
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
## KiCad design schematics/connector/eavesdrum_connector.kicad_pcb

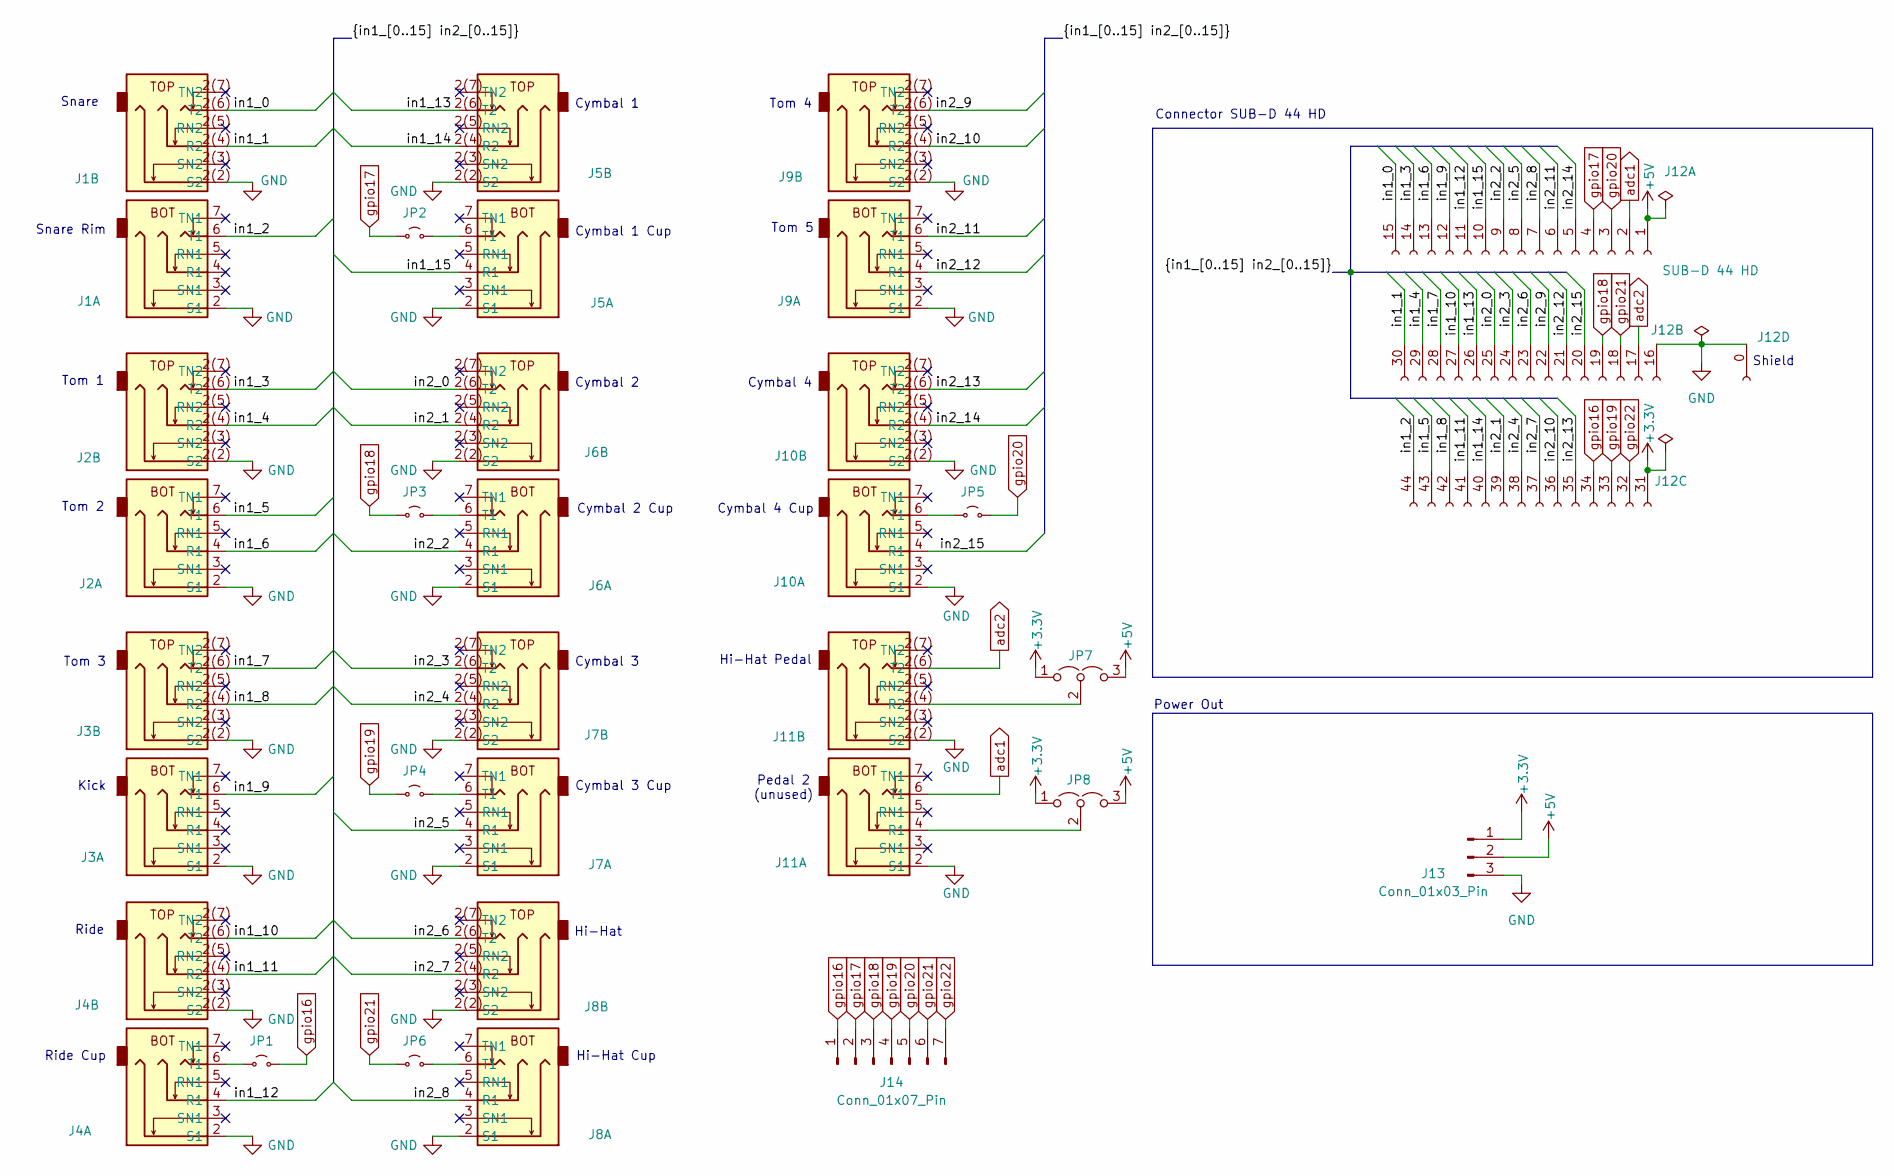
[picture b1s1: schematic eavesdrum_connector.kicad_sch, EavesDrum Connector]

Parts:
J1, J2, J3, J4, J5, J6, J7, J8, J9, J10, J11: AudioJack3_Dual_Ground_Switch; PJ-625K
J12: SUB-D 44 HD; DSUB-44-HD_Pins_Horizontal_P2.29x2.54mm_EdgePinOffset8.35mm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
J13: Conn_01x03_Pin; TerminalBlock_WAGO_233-503_2x03_P2.54mm
J14: Conn_01x07_Pin; TerminalBlock_WAGO_233-507_2x07_P2.54mm
JP1, JP2, JP3, JP4, JP5, JP6: Jumper_2_Small_Open; PinHeader_1x02_P2.54mm_Vertical
JP7, JP8: Jumper_3_Open; PinHeader_1x03_P2.54mm_Vertical

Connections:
+3.3V: J12.31, J13.1, JP7.1 (A), JP8.1 (A)
+5V: J12.1, J13.2, JP7.3 (B), JP8.3 (B)
/in1_0: J1.2(6) (T2), J12.15
/in1_1: J1.2(4) (R2), J12.30
/in1_2: J1.6 (T1), J12.44
/in1_3: J2.2(6) (T2), J12.14
/in1_4: J2.2(4) (R2), J12.29
/in1_5: J2.6 (T1), J12.43
/in1_6: J2.4 (R1), J12.13
/in1_7: J3.2(6) (T2), J12.28
/in1_8: J3.2(4) (R2), J12.42
/in1_9: J3.6 (T1), J12.12
/in1_10: J4.2(6) (T2), J12.27
/in1_11: J4.2(4) (R2), J12.41
/in1_12: J4.4 (R1), J12.11
/in1_13: J5.2(6) (T2), J12.26
/in1_14: J5.2(4) (R2), J12.40
/in1_15: J5.4 (R1), J12.10
/in2_0: J6.2(6) (T2), J12.25
/in2_1: J6.2(4) (R2), J12.39
/in2_2: J6.4 (R1), J12.9
/in2_3: J7.2(6) (T2), J12.24
/in2_4: J7.2(4) (R2), J12.38
/in2_5: J7.4 (R1), J12.8
/in2_6: J8.2(6) (T2), J12.23
/in2_7: J8.2(4) (R2), J12.37
/in2_8: J8.4 (R1), J12.7
/in2_9: J9.2(6) (T2), J12.22
/in2_10: J9.2(4) (R2), J12.36
/in2_11: J9.6 (T1), J12.6
/in2_12: J9.4 (R1), J12.21
/in2_13: J10.2(6) (T2), J12.35
/in2_14: J10.2(4) (R2), J12.5
/in2_15: J10.4 (R1), J12.20
GND: J1.2 (S1), J1.2(2) (S2), J2.2 (S1), J2.2(2) (S2), J3.2 (S1), J3.2(2) (S2), J4.2 (S1), J4.2(2) (S2), J5.2 (S1), J5.2(2) (S2), J6.2 (S1), J6.2(2) (S2), J7.2 (S1), J7.2(2) (S2), J8.2 (S1), J8.2(2) (S2), J9.2 (S1), J9.2(2) (S2), J10.2 (S1), J10.2(2) (S2), J11.2 (S1), J11.2(2) (S2), J12.0 (Pin_44), J12.16, J13.3
unnamed: J4.6 (T1), JP1.1 (A)
unnamed: J5.6 (T1), JP2.1 (A)
unnamed: J6.6 (T1), JP3.1 (A)
unnamed: J7.6 (T1), JP4.1 (A)
unnamed: J8.6 (T1), JP6.1 (A)
unnamed: J10.6 (T1), JP5.1 (A)
unnamed: J11.4 (R1), JP8.2 (C)
unnamed: J11.2(4) (R2), JP7.2 (C)
adc1: J11.6 (T1), J12.2
adc2: J11.2(6) (T2), J12.17
gpio16: J12.34, J14.1, JP1.2 (B)
gpio17: J12.4, J14.2, JP2.2 (B)
gpio18: J12.19, J14.3, JP3.2 (B)
gpio19: J12.33, J14.4, JP4.2 (B)
gpio20: J12.3, J14.5, JP5.2 (B)
gpio21: J12.18, J14.6, JP6.2 (B)
gpio22: J12.32, J14.7

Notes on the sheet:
Hi-Hat Cup
Connector SUB-D 44 HD
Snare
Shield
Ride Cup
Cymbal 2
Hi-Hat
Kick
Pedal 2 (unused)
Cymbal 4
Ride
Tom 3
Cymbal 1
Cymbal 2 Cup
Snare Rim
Tom 5
Power Out
Cymbal 4 Cup
Cymbal 1 Cup
Cymbal 3 Cup
Tom 1
Tom 4
Hi-Hat Pedal
Tom 2
Cymbal 3

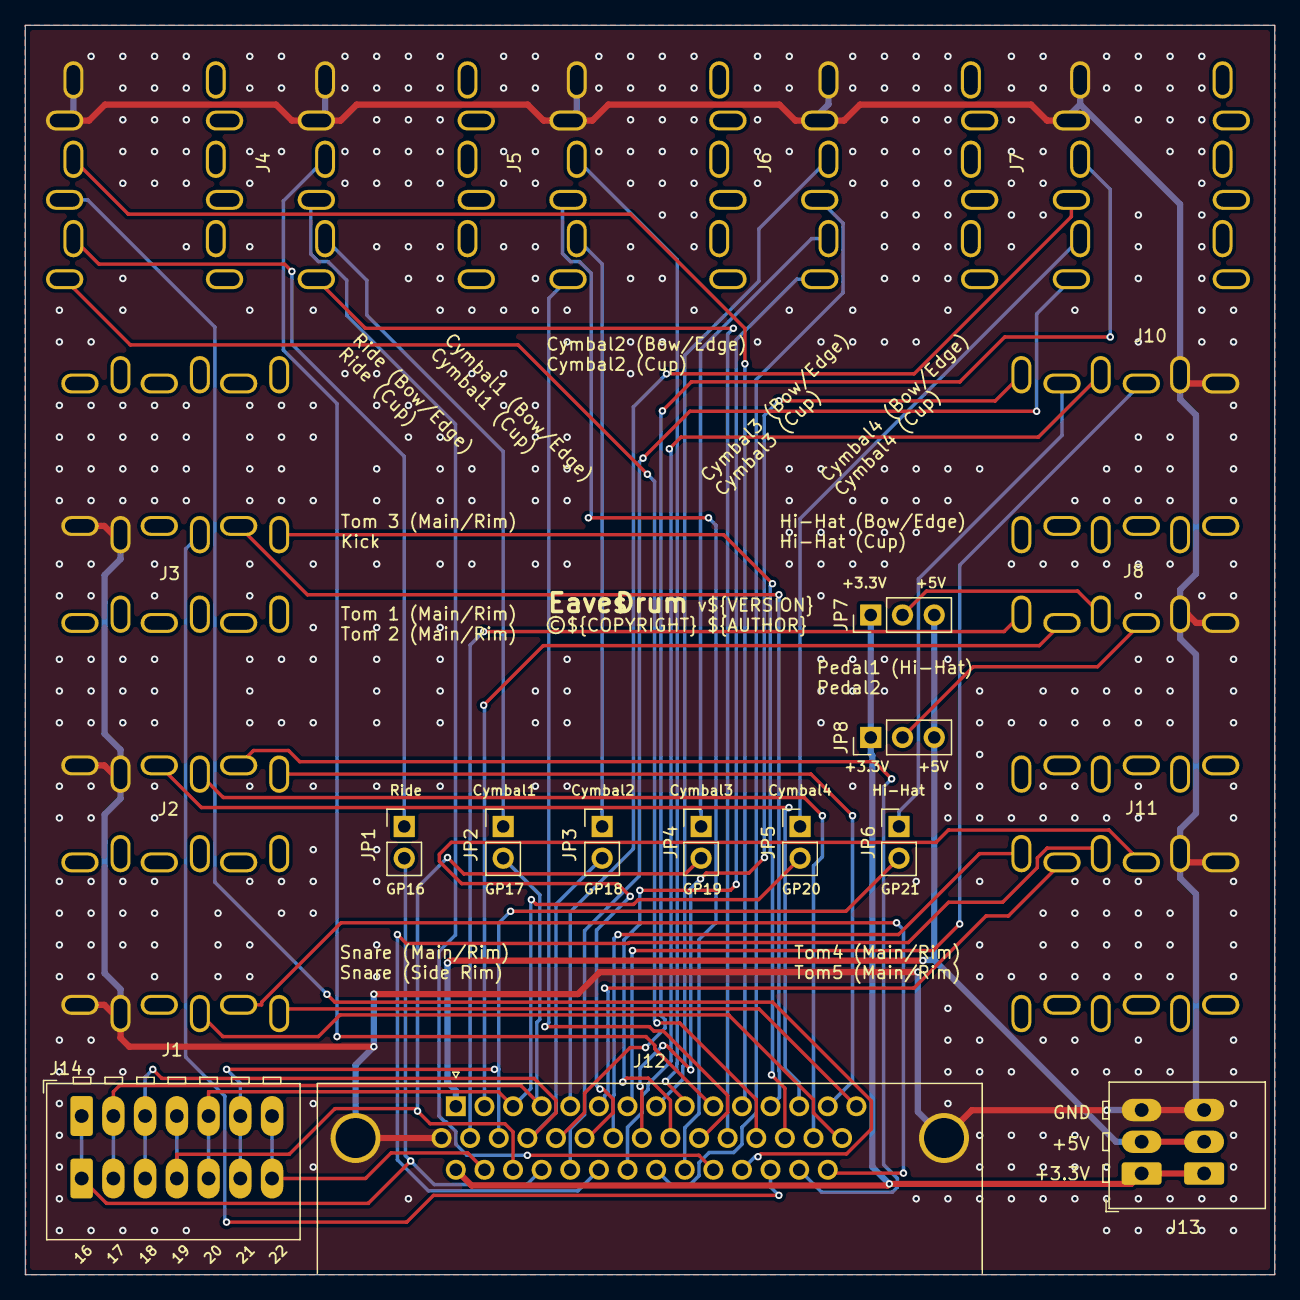
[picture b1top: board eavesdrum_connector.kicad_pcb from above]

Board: 2 copper layers, 100.0 x 100.0 mm, 22 parts (0 on the bottom side), 52 nets.

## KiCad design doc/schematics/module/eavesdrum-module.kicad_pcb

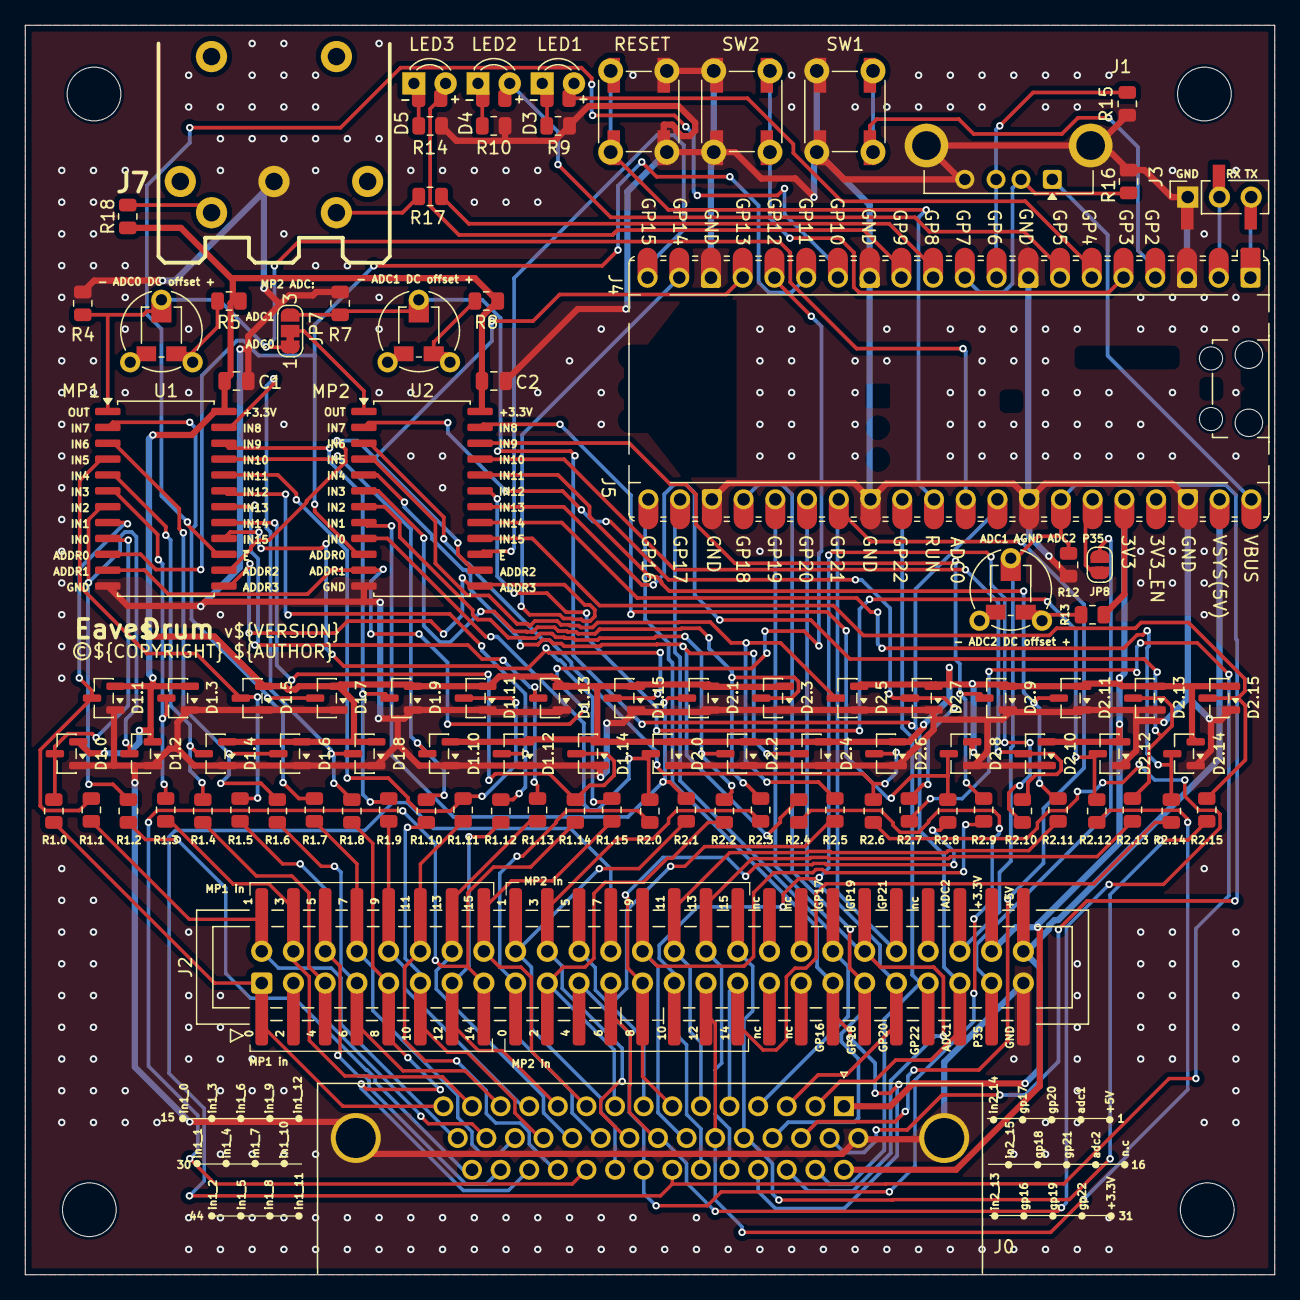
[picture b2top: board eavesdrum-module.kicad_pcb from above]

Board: 2 copper layers, 100.0 x 100.0 mm, 103 parts (0 on the bottom side), 106 nets.

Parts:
C1, C2: 10u; C_0805_2012Metric
D1.0, D1.1, D1.2, D1.3, D1.4, D1.5, D1.6, D1.7, D1.8, D1.9, D1.10, D1.11, D1.12, D1.13, D1.14, D1.15, D2.0, D2.1, D2.2, D2.3, D2.4, D2.5, D2.6, D2.7, D2.8, D2.9, D2.10, D2.11, D2.12, D2.13, D2.14, D2.15: BAT54S; SOT-23
D3: LED (red); LED_D3.0mm_SMD_Thru
D4: LED (white/blue); LED_D3.0mm_SMD_Thru
D5: LED (yellow); LED_D3.0mm_SMD_Thru
J0: SUB-D 44 HD; DSUB-44-HD_Socket_Horizontal_P2.29x2.54mm_EdgePinOffset8.35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
J1: USB_A; USB_A_Connfly_DS1095
J2: Conn_02x25_Odd_Even; IDC-Header_2x25_P2.54mm_Vertical_SMD_Thru
J3: Conn_01x03; PinSocket_1x03_P2.54mm_Vertical_SMD_Thru_Pin1Left
J4: Conn_01x20_Socket; RaspberryPi_Pico_wo_2nd_pin_row
J5: Conn_01x20_Socket; RaspberryPi_Pico_Common_2nd_pin_row
J7: DIN-5_180degree; MIDI_DIN5
JP7: Jumper_3; SolderJumper-3_P1.3mm_Bridged12_RoundedPad1.0x1.5mm_NumberL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
JP8: Jumper_2_Open; SolderJumper-2_P1.3mm_Open_RoundedPad1.0x1.5mm
M4_1, M4_2, M4_3, M4_4: MountingHole_4.3mm_M4
R1.0, R1.1, R1.2, R1.3, R1.4, R1.5, R1.6, R1.7, R1.8, R1.9, R1.10, R1.11, R1.12, R1.13, R1.14, R1.15, R2.0, R2.1, R2.2, R2.3, R2.4, R2.5, R2.6, R2.7, R2.8, R2.9, R2.10, R2.11, R2.12, R2.13, R2.14, R2.15: 1k; R_0805_2012Metric
R3, R6: 5k; Potentiometer_SMD_Thru_Vertical
R4, R7, R12: 2.7k; R_0805_2012Metric
R5, R8, R13: 330; R_0805_2012Metric
R9, R14: 4.7k; R_0805_2012Metric
R10: 10k; R_0805_2012Metric
R11: 100k; Potentiometer_SMD_Thru_Vertical
R15, R16: 15k; R_0805_2012Metric
R17: 10; R_0805_2012Metric
R18: 33; R_0805_2012Metric
SW1, SW2, SW3: SW_Push; SW_Push_SMD_Thru
U1, U2: CD74HC4067M; SOIC-24W_7.5x15.4mm_P1.27mm

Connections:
+3.3V: C1.1, C2.1, D1.0.2 (K), D1.1.2 (K), D1.2.2 (K), D1.3.2 (K), D1.4.2 (K), D1.5.2 (K), D1.6.2 (K), D1.7.2 (K), D1.8.2 (K), D1.9.2 (K), D1.10.2 (K), D1.11.2 (K), D1.12.2 (K), D1.13.2 (K), D1.14.2 (K), D1.15.2 (K), D2.0.2 (K), D2.1.2 (K), D2.2.2 (K), D2.3.2 (K), D2.4.2 (K), D2.5.2 (K), D2.6.2 (K), D2.7.2 (K), D2.8.2 (K), D2.9.2 (K), D2.10.2 (K), D2.11.2 (K), D2.12.2 (K), D2.13.2 (K), D2.14.2 (K), D2.15.2 (K), J0.31, J2.48, J5.5, R5.2, R8.2, R13.2, R18.1, U1.24 (VCC), U2.24 (VCC)
+5V: J0.1, J2.50, J5.2
/in1_0: J0.15, J2.1, R1.0.2
/in1_1: J0.30, J2.2, R1.1.2
/in1_2: J0.44, J2.3, R1.2.2
/in1_3: J0.14, J2.4, R1.3.2
/in1_4: J0.29, J2.5, R1.4.2
/in1_5: J0.43, J2.6, R1.5.2
/in1_6: J0.13, J2.7, R1.6.2
/in1_7: J0.28, J2.8, R1.7.2
/in1_8: J0.42, J2.9, R1.8.2
/in1_9: J0.12, J2.10, R1.9.2
/in1_10: J0.27, J2.11, R1.10.2
/in1_11: J0.41, J2.12, R1.11.2
/in1_12: J0.11, J2.13, R1.12.2
/in1_13: J0.26, J2.14, R1.13.2
/in1_14: J0.40, J2.15, R1.14.2
/in1_15: J0.10, J2.16, R1.15.2
/in2_0: J0.25, J2.17, R2.0.2
/in2_1: J0.39, J2.18, R2.1.2
/in2_2: J0.9, J2.19, R2.2.2
/in2_3: J0.24, J2.20, R2.3.2
/in2_4: J0.38, J2.21, R2.4.2
/in2_5: J0.8, J2.22, R2.5.2
/in2_6: J0.23, J2.23, R2.6.2
/in2_7: J0.37, J2.24, R2.7.2
/in2_8: J0.7, J2.25, R2.8.2
/in2_9: J0.22, J2.26, R2.9.2
/in2_10: J0.36, J2.27, R2.10.2
/in2_11: J0.6, J2.28, R2.11.2
/in2_12: J0.21, J2.29, R2.12.2
/in2_13: J0.35, J2.30, R2.13.2
/in2_14: J0.5, J2.31, R2.14.2
/in2_15: J0.20, J2.32, R2.15.2
ADC_Vref: J5.6, JP8.1 (A)
GND: C1.2, C2.2, D1.0.1 (A), D1.1.1 (A), D1.2.1 (A), D1.3.1 (A), D1.4.1 (A), D1.5.1 (A), D1.6.1 (A), D1.7.1 (A), D1.8.1 (A), D1.9.1 (A), D1.10.1 (A), D1.11.1 (A), D1.12.1 (A), D1.13.1 (A), D1.14.1 (A), D1.15.1 (A), D2.0.1 (A), D2.1.1 (A), D2.2.1 (A), D2.3.1 (A), D2.4.1 (A), D2.5.1 (A), D2.6.1 (A), D2.7.1 (A), D2.8.1 (A), D2.9.1 (A), D2.10.1 (A), D2.11.1 (A), D2.12.1 (A), D2.13.1 (A), D2.14.1 (A), D2.15.1 (A), J0.0 (Pin_44), J0.16, J1.4 (GND), J1.5 (Shield), J2.49, J3.1, J4.3, J4.8, J4.13, J4.18, J5.3, J5.8, J5.13, J5.18, J7.2, R4.1, R7.1, R9.2, R10.2, R12.1, R14.2, R15.2, R16.2, SW1.2, SW2.2, SW3.1, U1.12 (GND), U2.12 (GND)
unnamed: D1.0.3 (COM), R1.0.1, U1.9 (I0)
unnamed: D1.1.3 (COM), R1.1.1, U1.8 (I1)
unnamed: D1.2.3 (COM), R1.2.1, U1.7 (I2)
unnamed: D1.3.3 (COM), R1.3.1, U1.6 (I3)
unnamed: D1.4.3 (COM), R1.4.1, U1.5 (I4)
unnamed: D1.5.3 (COM), R1.5.1, U1.4 (I5)
unnamed: D1.6.3 (COM), R1.6.1, U1.3 (I6)
unnamed: D1.7.3 (COM), R1.7.1, U1.2 (I7)
unnamed: D1.8.3 (COM), R1.8.1, U1.23 (I8)
unnamed: D1.9.3 (COM), R1.9.1, U1.22 (I9)
unnamed: D1.10.3 (COM), R1.10.1, U1.21 (I10)
unnamed: D1.11.3 (COM), R1.11.1, U1.20 (I11)
unnamed: D1.12.3 (COM), R1.12.1, U1.19 (I12)
unnamed: D1.13.3 (COM), R1.13.1, U1.18 (I13)
unnamed: D1.14.3 (COM), R1.14.1, U1.17 (I14)
unnamed: D1.15.3 (COM), R1.15.1, U1.16 (I15)
unnamed: D2.0.3 (COM), R2.0.1, U2.9 (I0)
unnamed: D2.1.3 (COM), R2.1.1, U2.8 (I1)
unnamed: D2.2.3 (COM), R2.2.1, U2.7 (I2)
unnamed: D2.3.3 (COM), R2.3.1, U2.6 (I3)
unnamed: D2.4.3 (COM), R2.4.1, U2.5 (I4)
unnamed: D2.5.3 (COM), R2.5.1, U2.4 (I5)
unnamed: D2.6.3 (COM), R2.6.1, U2.3 (I6)
unnamed: D2.7.3 (COM), R2.7.1, U2.2 (I7)
unnamed: D2.8.3 (COM), R2.8.1, U2.23 (I8)
unnamed: D2.9.3 (COM), R2.9.1, U2.22 (I9)
unnamed: D2.10.3 (COM), R2.10.1, U2.21 (I10)
unnamed: D2.11.3 (COM), R2.11.1, U2.20 (I11)
unnamed: D2.12.3 (COM), R2.12.1, U2.19 (I12)
unnamed: D2.13.3 (COM), R2.13.1, U2.18 (I13)
unnamed: D2.14.3 (COM), R2.14.1, U2.17 (I14)
unnamed: D2.15.3 (COM), R2.15.1, U2.16 (I15)
unnamed: D3.1 (K), R9.1
unnamed: D4.1 (K), R10.1
unnamed: D5.1 (K), R14.1
unnamed: J2.47, JP8.2 (B)
unnamed: J7.4, R18.2
unnamed: J7.5, R17.2
unnamed: JP7.2 (C), U2.1 (COM)
unnamed: R3.1, R5.1
unnamed: R6.1, R8.1
unnamed: R11.1, R13.1
Vbus: J1.1 (VBUS), J5.1
adc0: J5.10, JP7.1 (A), R3.2, R4.2, U1.1 (COM)
adc1: J0.2, J2.45, J5.9, JP7.3 (B), R6.2, R7.2
adc2: J0.17, J2.46, J5.7, R11.2, R12.2
gpio0: J3.3, J4.1
gpio1: J3.2, J4.2
gpio2: J4.4, SW1.1
gpio3: J4.5, SW2.1
gpio4: D3.2 (A), J4.6
gpio5: D4.2 (A), J4.7
gpio6: J1.3 (D+), J4.9, R15.1
gpio7: J1.2 (D-), J4.10, R16.1
gpio8: J4.11, R17.1
gpio9: D5.2 (A), J4.12
gpio10: J4.14, U1.15 (~E)
gpio11: J4.15, U1.10 (S0), U2.10 (S0)
gpio12: J4.16, U1.11 (S1), U2.11 (S1)
gpio13: J4.17, U1.14 (S2), U2.14 (S2)
gpio14: J4.19, U1.13 (S3), U2.13 (S3)
gpio15: J4.20, U2.15 (~E)
gpio16: J0.34, J2.37, J5.20
gpio17: J0.4, J2.38, J5.19
gpio18: J0.19, J2.39, J5.17
gpio19: J0.33, J2.40, J5.16
gpio20: J0.3, J2.41, J5.15
gpio21: J0.18, J2.42, J5.14
gpio22: J0.32, J2.43, J5.12
run: J5.11, SW3.2

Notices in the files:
README.md:
This project is licensed under the [GNU General Public License v3.0](LICENSE.txt).
The licenses of the used libraries can be viewed by clicking on the info-button in the top icon bar.
Logo Fonts:
- Audiowide
- https://fonts.google.com/specimen/Audiowide
- Copyright (c) 2012, Brian J. Bonislawsky DBA Astigmatic (AOETI) (astigma@astigmatic.com)
- SIL Open Font License, Version 1.1
- Philosopher
- https://fonts.google.com/specimen/Philosopher
- Designed by Jovanny Lemonad
- Copyright 2011 The Philosopher Project Authors (https://github.com/alexeiva/philosopher)
- SIL Open Font
